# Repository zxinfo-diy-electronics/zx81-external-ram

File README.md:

# zx81-external-ram module 16K/32K
Simple and compact external RAM interface for the ZX81 with WRX compability. First version is a 16K module and can be used on ZX80 and Lambda 8300 or simlar as well. The interface is made using THT components, making it easy for everyone to make.

The interface has been tested with the following 32K SRAM chips, all running Beamrider perfectly.
- UM62256E-70LL
- HM62256BLP-10
- AS6C62256-55PCN

| <!---> | <!---> |
| ------ | ------ |
|||

## version 1.2 - minor modification
It turns out that v1.1 does not work together with the zx81-external-eprom interface, due to issues with the ROMCS line that can be fixed with a diode on the ROMCS line. The schema has been updated with this fix, but if you already have a v1.1 PCB it's easy to do the fix.

- Cut the ROMCS trace on the back - and put in a diode, eg. 1N4148 instead - as shown here:

And now it runs fine with the zx81-external-eprom interface as well.

BOM for v1.2 (ROMCS fix)
- same as v1.1
- Diode 1N4144 (or similar)

## version 1.1 - full 32K support, with data in the 32-48K area.
Most version for internal 32K RAM puts the extra 16K at the top, 48 to 64K - but this is not what most 32K program expects. The 32K programs I have found expect the 32K from 16K, which requires some extra logic - another issue with this configuration is that normaly the ROM is mirrored between 32 and 48K, which means the ROM has to be disabled when the ZX81 access this part of the memory. I also decided to change the diodes from 1N4148 to BAT85 as suggested in general for this type of usage.

A little prototyping based on the v1.0 board - and yes, 32K from adress 16384 is all good here tested with Beamrider that require 32K and WRX :-)
| <!---> | <!---> |
| ------ | ------ |
|||

### Test using SYSINFO.P v0.02
This test program examines the memory configuration and reports this, 32K ram starting from address 0x4000 :-)

### Programs tested with success so far:
- [Beamrider](https://problemkaputt.de/beamride.htm), 32K and WRX graphics 
- [MaxDemo](https://demozoo.org/productions/159644/), 32K and WRX graphics (impressive 320x240 resolution)
- [Cross Snake](https://github.com/Fabrizio-Caruso/CROSS-LIB/releases/tag/XSnake2.0), 32K and WRX
- [Cross Chase](https://github.com/Fabrizio-Caruso/CROSS-LIB/releases/tag/WRX), 32K and WRX
- [Space Invaders](https://splintergu.itch.io/space-invaders-for-zx81-wrx), 32K and WRX

32K Programs NOT working - as they require internal modification in order to run M/C above 32K area.
- [The Crystal Frog](https://www.sinclairzxworld.com/viewtopic.php?t=334)

BOM for v1.1 (32K, continously from adress 16384)
- LED 3mm
- Resistor 470 Ohm
- Resistor 4K7 Ohm
- Resistor 10K Ohm
- 2 x Ceramic capacitor 100nF, P2,54
- 1 x Ceramic capacitor 1,2nF, P2,54
- 2 x Diode BAT85
- 74LS00
- 74LS32
- RAM 62256 or similar
- ZX81 Edge Connector or my [ZX81 Bus Extender](https://github.com/thomasheckmann/zx81-bus-extender)

## version 1.0 - 16K with WRX support
The interface for now is only using 16K from the 62256 memory chip, using the other half 16K might be added on later version. I might also consider making a SMD version, making it even smaller in size :-)

| SCHEMA | PCB |
| ------ | --- |
|||

The PCB arrived, so I populated it with some components (all written on the silkscreen).

BOM for v1.0 (16K only)
- LED 3mm
- Resistor 470 Ohm
- Resistor 4K7 Ohm
- 2 x Ceramic capacitor 100nF, P2,54
- 2 x Diode 1N4148
- 74LS00
- RAM 62256 or similar
- ZX81 Edge Connector or my [ZX81 Bus Extender](https://github.com/thomasheckmann/zx81-bus-extender)
  
NOTE: WRX hi-res, to get full support for hi-res WRX a cercamic capacitor is needed between PIN 20 (CS) and GND. In this build with a KM62256ALP-10 a 1,2nF ceramic capacitor should be fitted. 

The value for the capacitor for different 62256 SRAM chips tested with [STARFIGHT](https://problemkaputt.de/starfigh.htm)

- KM62256ALP-10, 1.2nF

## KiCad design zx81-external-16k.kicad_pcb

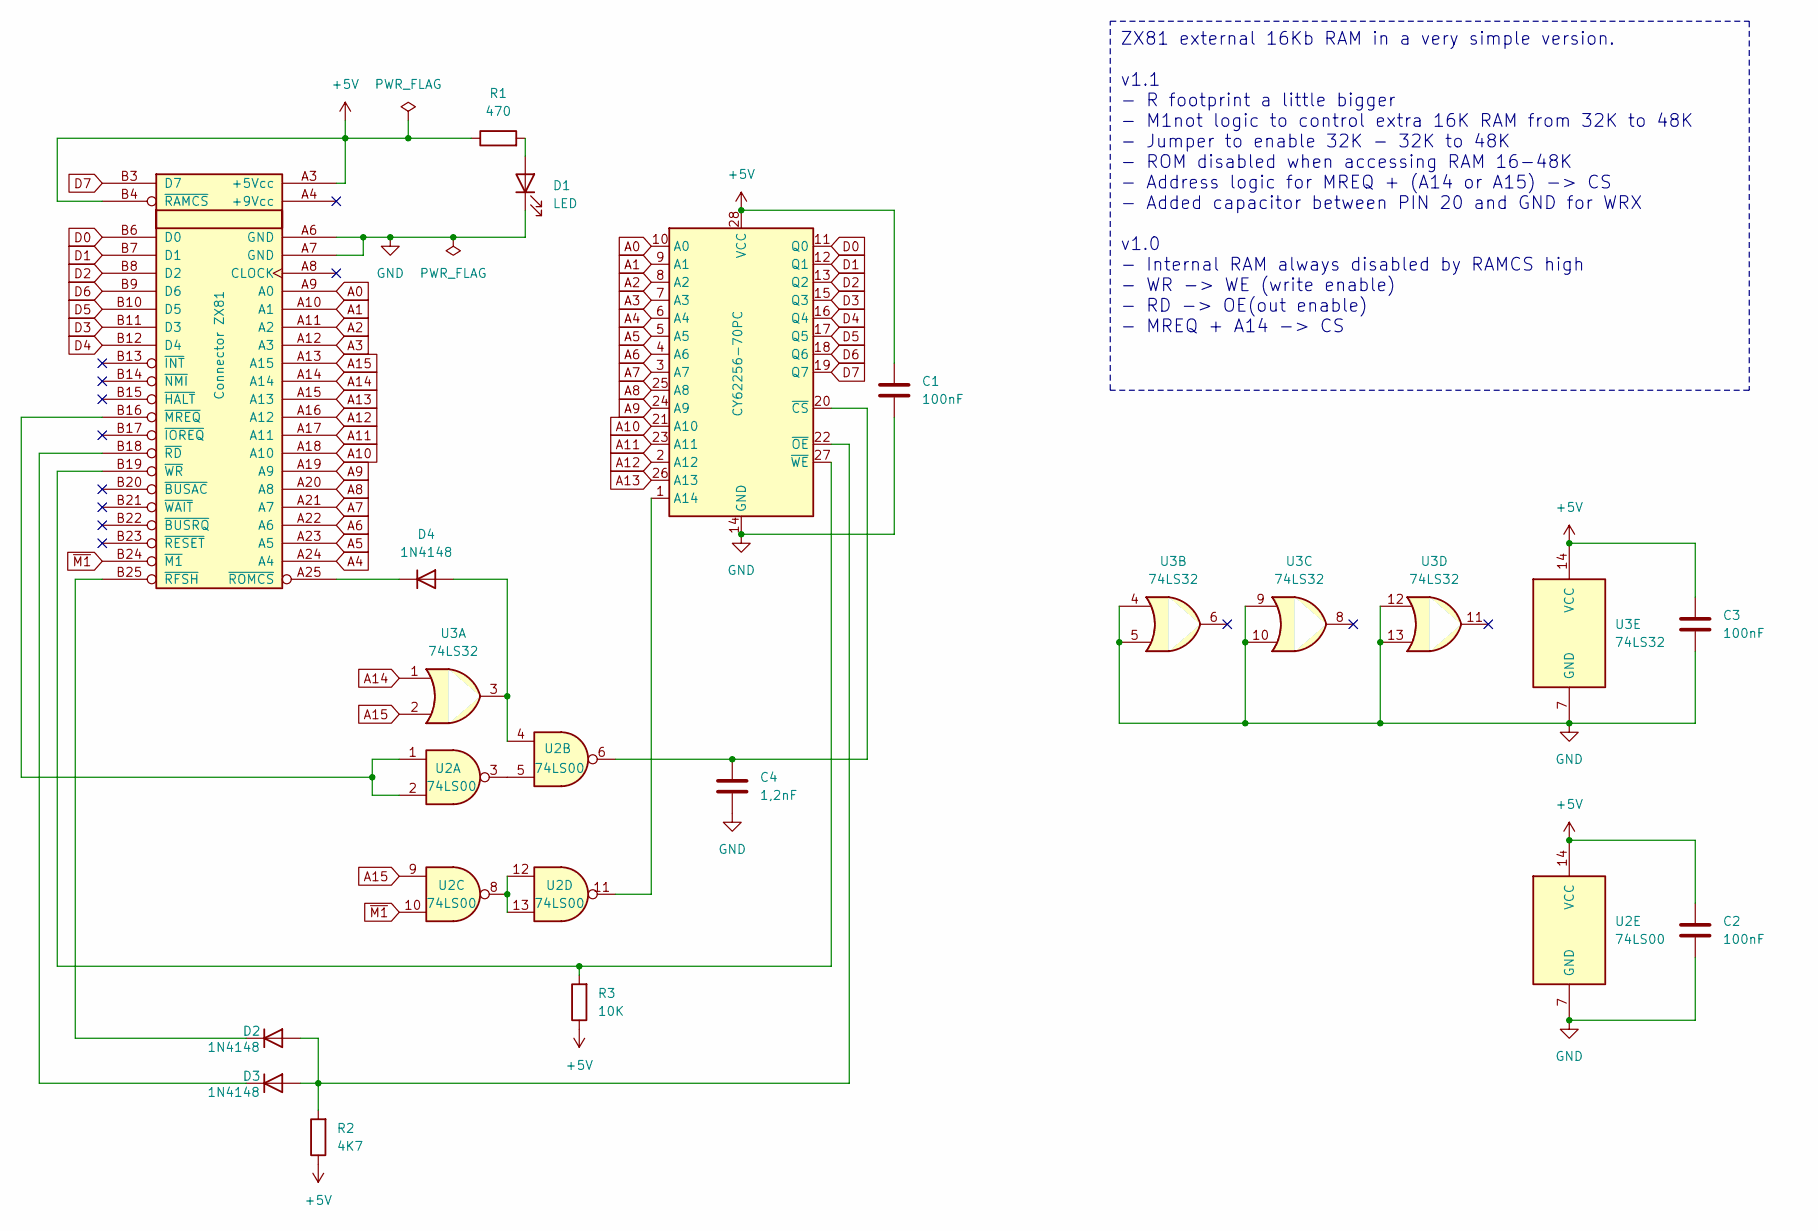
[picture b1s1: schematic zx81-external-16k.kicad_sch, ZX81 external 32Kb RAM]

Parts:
C1, C2, C3: 100nF; C_Disc_D3.0mm_W1.6mm_P2.50mm
C4: 1,2nF; C_Disc_D3.0mm_W1.6mm_P2.50mm
D1: LED; LED_D3.0mm
D2, D3, D4: 1N4148; D_DO-35_SOD27_P7.62mm_Horizontal
J1: Connector ZX81; EDGE ZX81 BOTTOM
R1: 470; R_Axial_DIN0207_L6.3mm_D2.5mm_P10.16mm_Horizontal
R2: 4K7; R_Axial_DIN0207_L6.3mm_D2.5mm_P10.16mm_Horizontal
R3: 10K; R_Axial_DIN0207_L6.3mm_D2.5mm_P10.16mm_Horizontal
U1: CY62256-70PC; DIP-28_W15.24mm
U2: 74LS00; DIP-14_W7.62mm
U3: 74LS32; DIP-14_W7.62mm

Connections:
+5V: C1.1, C2.1, C3.1, J1.A3 (+5Vcc), J1.B4 (~RAMCS), R1.1, R2.1, R3.1, U1.28 (VCC), U2.14 (VCC), U3.14 (VCC)
A0: J1.A9 (A0), U1.10 (A0)
A1: J1.A10 (A1), U1.9 (A1)
A2: J1.A11 (A2), U1.8 (A2)
A3: J1.A12 (A3), U1.7 (A3)
A4: J1.A24 (A4), U1.6 (A4)
A5: J1.A23 (A5), U1.5 (A5)
A6: J1.A22 (A6), U1.4 (A6)
A7: J1.A21 (A7), U1.3 (A7)
A8: J1.A20 (A8), U1.25 (A8)
A9: J1.A19 (A9), U1.24 (A9)
A10: J1.A18 (A10), U1.21 (A10)
A11: J1.A17 (A11), U1.23 (A11)
A12: J1.A16 (A12), U1.2 (A12)
A13: J1.A15 (A13), U1.26 (A13)
A14: J1.A14, U3.1
A15: J1.A13 (A15), U2.9, U3.2
D0: J1.B6 (D0), U1.11 (Q0)
D1: J1.B7 (D1), U1.12 (Q1)
D2: J1.B8 (D2), U1.13 (Q2)
D3: J1.B11 (D3), U1.15 (Q3)
D4: J1.B12 (D4), U1.16 (Q4)
D5: J1.B10 (D5), U1.17 (Q5)
D6: J1.B9 (D6), U1.18 (Q6)
D7: J1.B3 (D7), U1.19 (Q7)
GND: C1.2, C2.2, C3.2, C4.2, D1.1 (K), J1.A6 (GND), J1.A7 (GND), U1.14 (GND), U2.7 (GND), U3.4, U3.5, U3.7 (GND), U3.9, U3.10, U3.12, U3.13
unnamed: D1.2 (A), R1.2
unnamed: D2.2 (A), D3.2 (A), R2.2, U1.22 (~OE)
unnamed: D2.1 (K), J1.B25 (~RFSH)
unnamed: D3.1 (K), J1.B18 (~RD)
unnamed: D4.2 (A), U2.4, U3.3
unnamed: D4.1 (K), J1.A25 (~ROMCS)
unnamed: J1.B16 (~MREQ), U2.1, U2.2
unnamed: J1.B19 (~WR), R3.2, U1.27 (~WE)
unnamed: U1.1 (A14), U2.11
unnamed: C4.1, U1.20 (~CS), U2.6
unnamed: U2.3, U2.5
unnamed: U2.8, U2.12, U2.13
~M1: J1.B24 (~M1), U2.10

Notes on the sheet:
ZX81 external 16Kb RAM in a very simple version. v1.1 - R footprint a little bigger - M1not logic to control extra 16K RAM from 32K to 48K - Jumper to enable 32K - 32K to 48K - ROM disabled when accessing RAM 16-48K - Address logic for MREQ + (A14 or A15) -> CS - Added capacitor between PIN 20 and 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

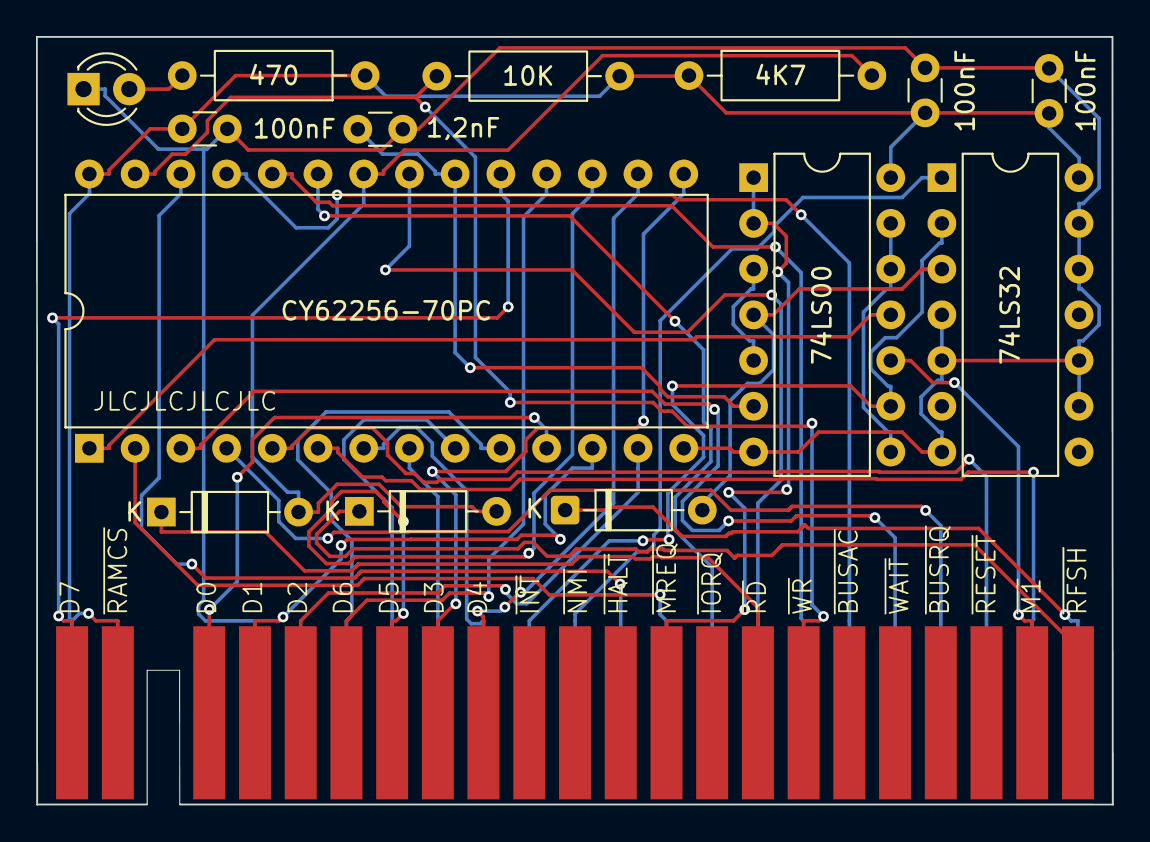
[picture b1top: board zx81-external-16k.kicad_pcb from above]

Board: 2 copper layers, 59.8 x 42.7 mm, 15 parts (0 on the bottom side), 39 nets.

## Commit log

2026-03-22 KiCad update
2026-03-22 Update README for zx81-external-ram module details
2026-03-22 Update README with version 1.2 changes
    Added details about version 1.2 modifications and fixes for the zx81-external-eprom interface.
2026-03-22 Update README with BOM for v1.2 and version details
    Added BOM for v1.2 and updated version 1.1 details.
2026-03-22 Update README with images and version 1.2 info
    Added images to README and updated version 1.2 details.
